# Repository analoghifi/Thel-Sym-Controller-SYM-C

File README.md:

# Thel Sym-Controller SYM-C
High-end balancer/debalancer with 'ransformer properties'  
(can be used to convert single ended to balanced or vice versa / with adjustable gain [in 5 steps])  
  
https://web.archive.org/web/20160126024454/http://www.thel-audioworld.de/module/HQ-SYM/Symmetrierer.htm  
https://web.archive.org/web/20210619130423/http://thel-audioworld.de/module/HQ-SYM/Symmetrierer.htm  
  
----  
### Kicad projects in this repo:  
* [Thel-Sym-Controller-SYM-C](https://github.com/analoghifi/Thel-Sym-Controller-SYM-C/tree/main/hardware/KiCad/original) | state: initial release v1.01 | like the original, 1-layer, THT

----

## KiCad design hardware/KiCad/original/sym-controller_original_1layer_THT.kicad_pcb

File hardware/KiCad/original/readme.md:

this is not the original Thel PCB but it's very like\* the original with the following exceptions:  
* slightly different board dimensions original: 47mm x 80mm -> this PCB: 47mm x 81mm
* sightly different mounting hole spacing original: 40mm x 73mm -> this PCB: 40mm x 74mm
* more massive ground and power supply PCB tracks  
* using the 2mm gold-plated brass solder pins (the same ones used on the more expensive Thel modules)
* different arrangement of the two GND output pins
* using a combined 5.0mm/7.5mm pin spacing footprint for the foil caps (C3,C8)  
* using a combined 2.5mm/5.0mm pin spacing footprint for the small ceramic caps (C1,C2,C6,C7)  
  
\*(same schematic / same 1-layer\** layout THT / same THT components in the same places on the board)  
\**(strictly speaking, this KiCad PCB is a two-layer PCB with plated-through holes, but you can also (let) produce it as a classic 1-layer PCB with non-plated holes if you wish, since all the tracks are on the bottom side only)  
  
----  
  
these are KiCad 6.x projects  
see how to get the proper 3D-Models from here: https://github.com/analoghifi/KiCad-3D-Models  

use kicanvas.org to view this KiCad project in your browser:  
https://kicanvas.org/?github=https%3A%2F%2Fgithub.com%2Fanaloghifi%2FThel-Sym-Controller-SYM-C%2Ftree%2Fmain%2Fhardware%2FKiCad%2Foriginal

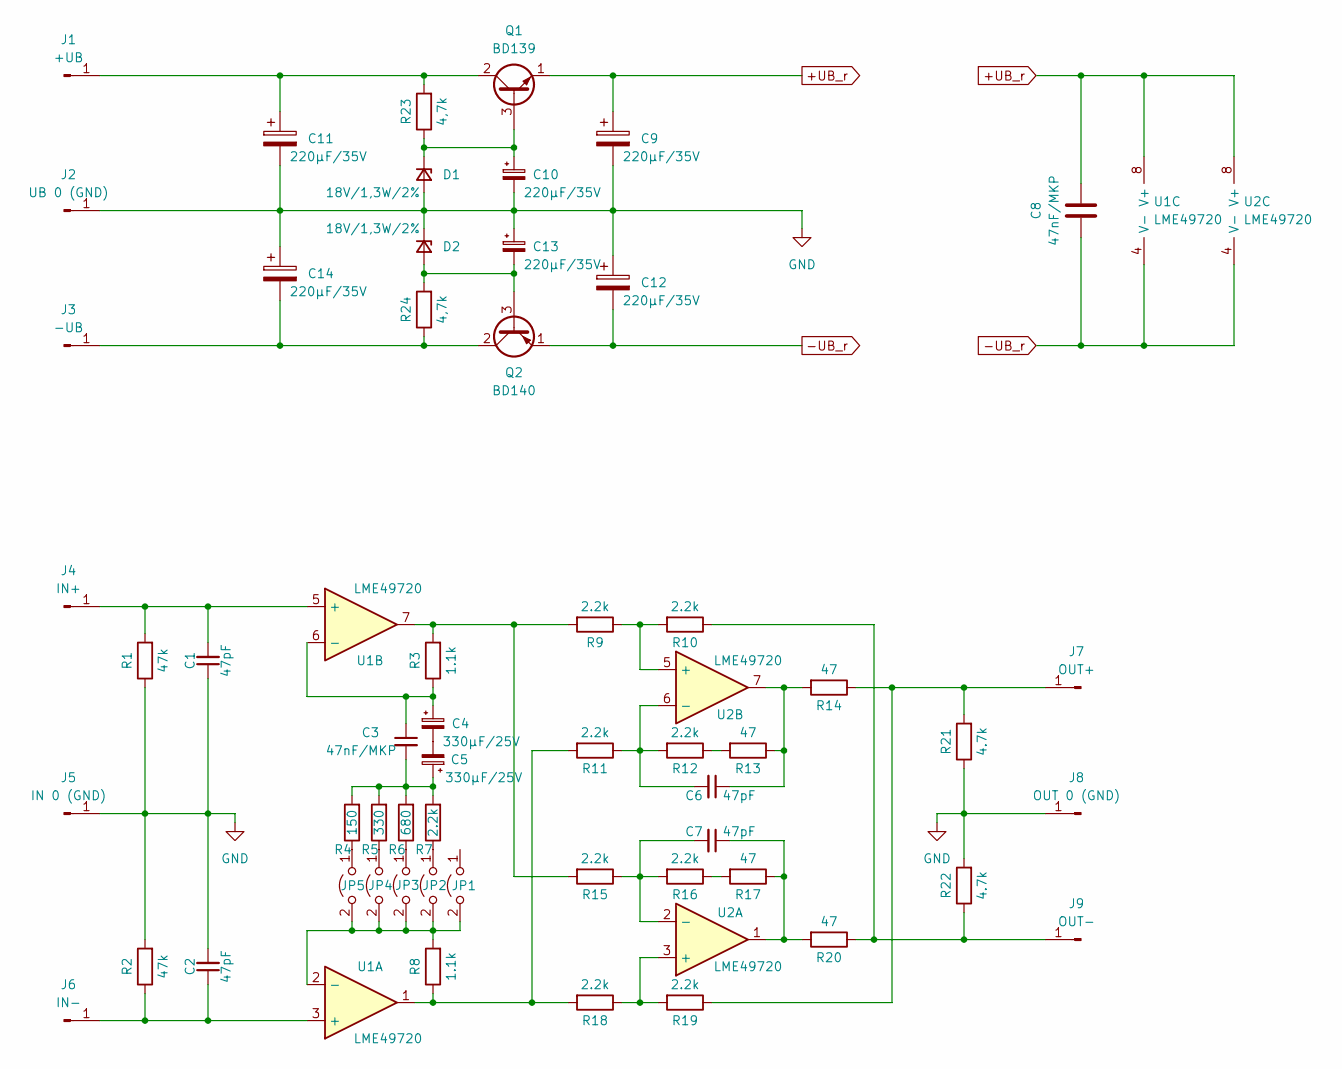
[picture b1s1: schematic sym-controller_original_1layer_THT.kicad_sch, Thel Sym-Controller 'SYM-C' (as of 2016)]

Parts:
C1, C2, C6, C7: 47pF; C_Rect_L7.0mm_W2.5mm_P2.50_5.00mm_min_silk
C3, C8: 47nF/MKP; C_Rect_L10.0mm_W4.0mm_P5.00_P7.50mm
C4, C5: 330µF/25V; CP_Radial_Black_D8.2mm_H12.0mm_P3.50mm_minimal_silk
C9, C10, C11, C12, C13, C14: 220µF/35V; CP_Radial_Black_D8.2mm_H12.0mm_P3.50mm_minimal_silk
D1, D2: 18V/1,3W/2%; D_DO-41_SOD81_P10.16mm_Horizontal_minSilk
J1: +UB; Loet_Pin_D1.5mm_L14.0mm
J2: UB 0 (GND); Loet_Pin_D1.5mm_L14.0mm
J3: -UB; Loet_Pin_D1.5mm_L14.0mm
J4: IN+; Loet_Pin_D1.5mm_L14.0mm
J5: IN 0 (GND); Loet_Pin_D1.5mm_L14.0mm
J6: IN-; Loet_Pin_D1.5mm_L14.0mm
J7: OUT+; Loet_Pin_D1.5mm_L14.0mm
J8: OUT 0 (GND); Loet_Pin_D1.5mm_L14.0mm
J9: OUT-; Loet_Pin_D1.5mm_L14.0mm
JP1, JP2, JP3, JP4, JP5: Jumper_2_Open; PinHeader_1x02_P2.54mm_Vertical
Q1: BD139; TO-126-3_Vertical
Q2: BD140; TO-126-3_Vertical
R1, R2: 47k; R_Axial_DIN0207_L6.3mm_D2.5mm_P10.16mm_Horizontal_minSilk
R3, R8: 1.1k; R_Axial_DIN0207_L6.3mm_D2.5mm_P10.16mm_Horizontal_minSilk
R4: 150; R_Axial_DIN0207_L6.3mm_D2.5mm_P10.16mm_Horizontal_minSilk
R5: 330; R_Axial_DIN0207_L6.3mm_D2.5mm_P10.16mm_Horizontal_minSilk
R6: 680; R_Axial_DIN0207_L6.3mm_D2.5mm_P10.16mm_Horizontal_minSilk
R7, R9, R10, R11, R12, R15, R16, R18, R19: 2.2k; R_Axial_DIN0207_L6.3mm_D2.5mm_P10.16mm_Horizontal_minSilk
R13, R14, R17, R20: 47; R_Axial_DIN0207_L6.3mm_D2.5mm_P10.16mm_Horizontal_minSilk
R21, R22: 4.7k; R_Axial_DIN0207_L6.3mm_D2.5mm_P10.16mm_Horizontal_minSilk
R23, R24: 4,7k; R_Axial_DIN0207_L6.3mm_D2.5mm_P10.16mm_Horizontal_minSilk
U1, U2: LME49720; DIP-8_W7.62mm

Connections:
+UB_r: C8.1, C9.1, Q1.1 (E), U1.8 (V+), U2.8 (V+)
-UB_r: C8.2, C12.2, Q2.1 (E), U1.4 (V-), U2.4 (V-)
GND: C1.1, C2.2, C9.2, C10.2, C11.2, C12.1, C13.1, C14.1, D1.2 (A), D2.1 (K), J2.1, J5.1, J8.1, R1.1, R2.2, R21.1, R22.2
unnamed: C1.2, J4.1, R1.2, U1.5 (+)
unnamed: C4.2, C5.2
unnamed: C3.2, C5.1, R4.2, R5.2, R6.2, R7.2
unnamed: C10.1, D1.1 (K), Q1.3 (B), R23.1
unnamed: C11.1, J1.1, Q1.2 (C), R23.2
unnamed: C13.2, D2.2 (A), Q2.3 (B), R24.2
unnamed: C14.2, J3.1, Q2.2 (C), R24.1
unnamed: J7.1, R14.1, R19.1, R21.2
unnamed: J9.1, R10.1, R20.1, R22.1
unnamed: JP5.1 (A), R4.1
unnamed: JP4.1 (A), R5.1
unnamed: JP3.1 (A), R6.1
unnamed: JP2.1 (A), R7.1
unnamed: R9.1, R10.2, U2.5 (+)
unnamed: R12.1, R13.2
unnamed: R16.1, R17.2
unnamed: R8.1, R11.2, R18.2, U1.1
unnamed: JP1.2 (B), JP2.2 (B), JP3.2 (B), JP4.2 (B), JP5.2 (B), R8.2, U1.2 (-)
unnamed: C2.1, J6.1, R2.1, U1.3 (+)
unnamed: C3.1, C4.1, R3.1, U1.6 (-)
unnamed: R3.2, R9.2, R15.2, U1.7
unnamed: C7.1, R17.1, R20.2, U2.1
unnamed: C7.2, R15.1, R16.2, U2.2 (-)
unnamed: R18.1, R19.2, U2.3 (+)
unnamed: C6.2, R11.1, R12.2, U2.6 (-)
unnamed: C6.1, R13.1, R14.2, U2.7

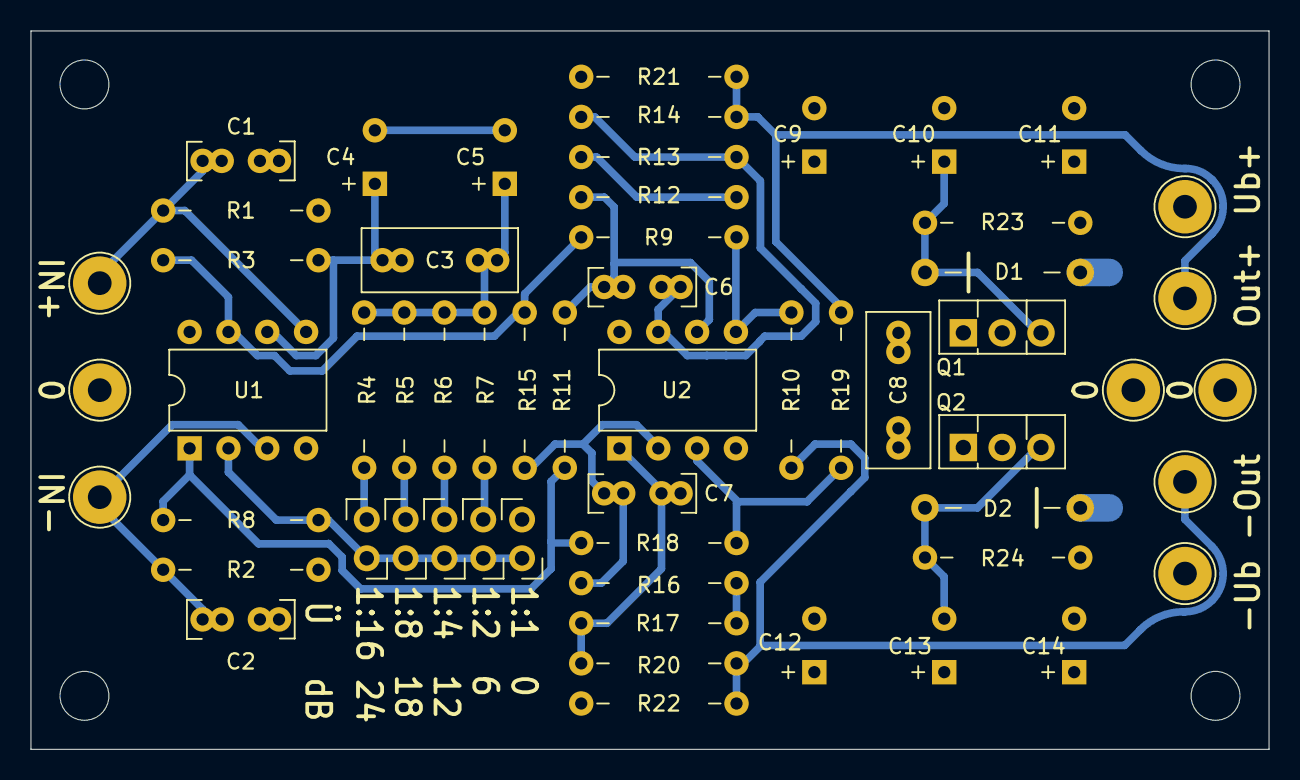
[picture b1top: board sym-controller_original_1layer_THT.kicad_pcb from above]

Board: 2 copper layers, 81.0 x 47.0 mm, 58 parts (0 on the bottom side), 29 nets.
